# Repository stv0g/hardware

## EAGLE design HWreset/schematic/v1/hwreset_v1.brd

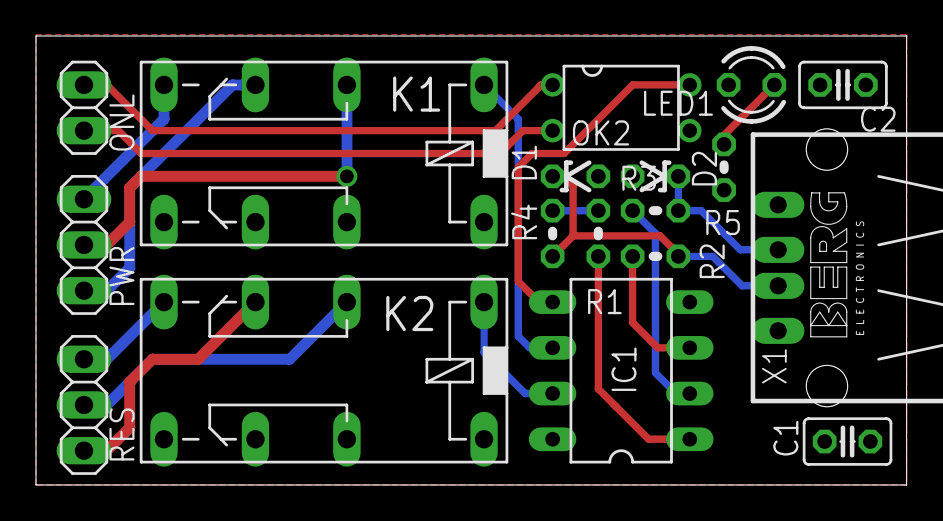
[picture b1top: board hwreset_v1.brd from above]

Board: 2 copper layers, 48.4 x 24.9 mm, 18 parts (0 on the bottom side), 19 nets.

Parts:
C1, C2: 100n; C025-025X050
D1, D2: 3.3; ZDIO-2.5
IC1: TINY22P; DIL08
K1, K2: 351
LED1: LED3MM
OK2: SFH618A-3; DIP4
ONL: 1X02
PWR: 1X03
R1: 5k; 0204V
R2, R3: 68; 0204V
R4: 2k2; 0204V
R5: 200; 0204V
RES: 1X03
X1: PN87520

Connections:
+5V: C1.1, C2.1, IC1.8, R1.1, R4.2, R5.1, X1.1
GND: C1.2, C2.2, D1.A, IC1.4, K1.16, K2.16, LED1.K, OK2.3, X1.4
unnamed: IC1.1, R1.2
unnamed: IC1.6, K1.1
unnamed: K2.P1, RES.2
unnamed: IC1.3, R2.1
unnamed: IC1.2, R3.1
unnamed: K1.P1, PWR.2
unnamed: D1.C, R2.2, R4.1, X1.2
unnamed: D2.C, R3.2, X1.3
unnamed: K1.O1, PWR.1
unnamed: K1.S1, PWR.3
unnamed: K2.O1, RES.1
unnamed: K2.S1, RES.3
unnamed: OK2.1, ONL.2
unnamed: OK2.2, ONL.1
unnamed: IC1.5, OK2.4
unnamed: LED1.A, R5.2
ON: IC1.7, K2.1

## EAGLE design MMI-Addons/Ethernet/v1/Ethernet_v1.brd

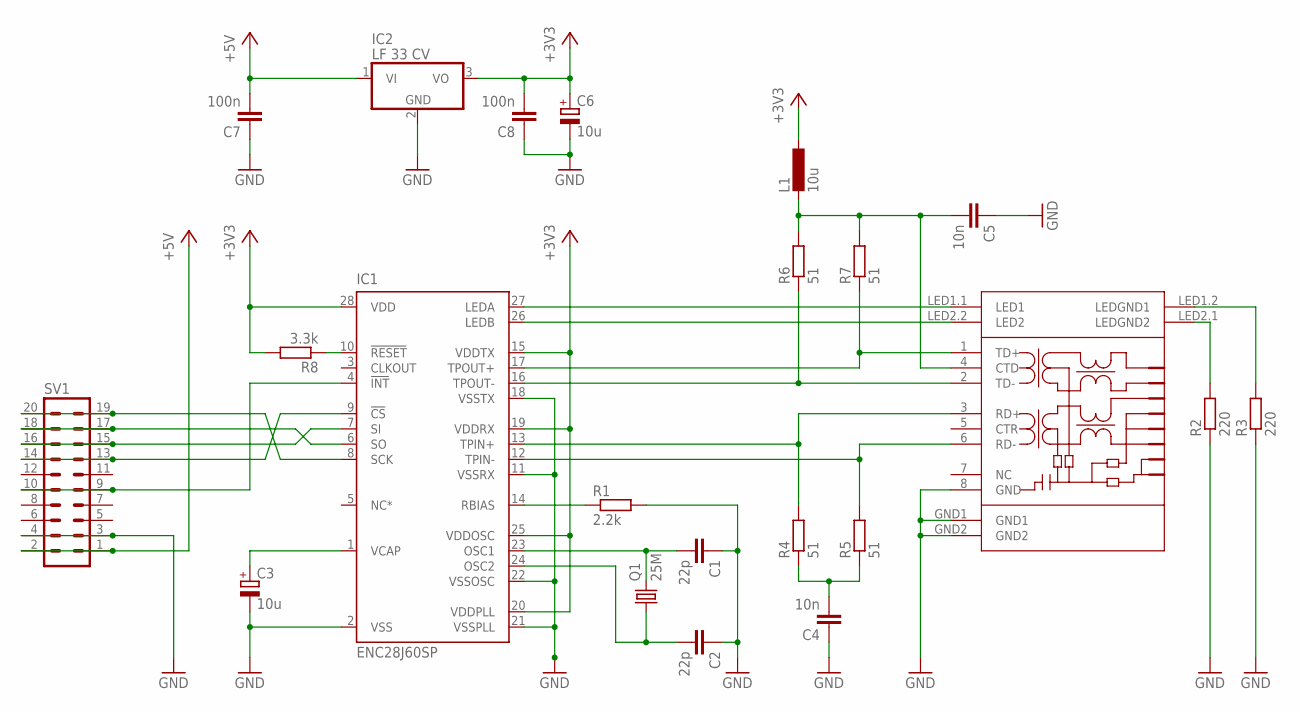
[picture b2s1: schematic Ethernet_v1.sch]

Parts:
C1, C2: 22p; C025-024X044
C3, C6: 10u; E2-5
C4, C5: 10n; C025-025X050
C7, C8: 100n; C025-025X050
IC1: ENC28J60SP; DIL28-3
IC2: LF 33 CV; TO220V
L1: 10u; 0207/10
Q1: 25M; HC49U-V
R1: 2.2k; 0207/2V
R2, R3: 220; 0207/2V
R4, R5, R6, R7: 51; 0207/2V
R8: 3.3k; 0207/2V
SV1: MA10-2W
U$1: TRJ0011

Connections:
+3V3: C6.+, C8.2, IC1.15 (VDDTX), IC1.19 (VDDRX), IC1.20 (VDDPLL), IC1.25 (VDDOSC), IC1.28 (VDD), IC2.3 (VO), L1.1, R8.2
+5V: C7.2, IC2.1 (VI), SV1.1, SV1.2
GND: C1.1, C2.1, C3.-, C4.1, C5.1, C6.-, C7.1, C8.1, IC1.2 (VSS), IC1.11 (VSSRX), IC1.18 (VSSTX), IC1.21 (VSSPLL), IC1.22 (VSSOSC), IC2.2 (GND), R1.2, R2.1, R3.1, SV1.3, SV1.4, U$1.8 (GND), U$1.GND1, U$1.GND2
unnamed: IC1.27 (LEDA), U$1.LED1.1 (LED1)
unnamed: IC1.26 (LEDB), U$1.LED2.2 (LED2)
unnamed: IC1.17 (TPOUT+), R7.1, U$1.1 (TD+)
unnamed: IC1.16 (TPOUT-), R6.1, U$1.2 (TD-)
unnamed: IC1.13 (TPIN+), R4.2, U$1.3 (RD+)
unnamed: IC1.12 (TPIN-), R5.2, U$1.6 (RD-)
unnamed: R2.2, U$1.LED2.1 (LEDGND2)
unnamed: C1.2, IC1.23 (OSC1), Q1.2
unnamed: IC1.14 (RBIAS), R1.1
unnamed: C2.2, IC1.24 (OSC2), Q1.1
unnamed: R3.2, U$1.LED1.2 (LEDGND1)
unnamed: C3.+, IC1.1 (VCAP)
unnamed: C4.2, R4.1, R5.1
unnamed: C5.2, L1.2, R6.2, R7.2, U$1.4 (CTD)
unnamed: IC1.10 (!RESET), R8.1
unnamed: IC1.4 (!INT), SV1.9, SV1.10
unnamed: IC1.8 (SCK), SV1.19, SV1.20
unnamed: IC1.6 (SO), SV1.17, SV1.18
unnamed: IC1.7 (SI), SV1.15, SV1.16
unnamed: IC1.9 (!CS), SV1.13, SV1.14

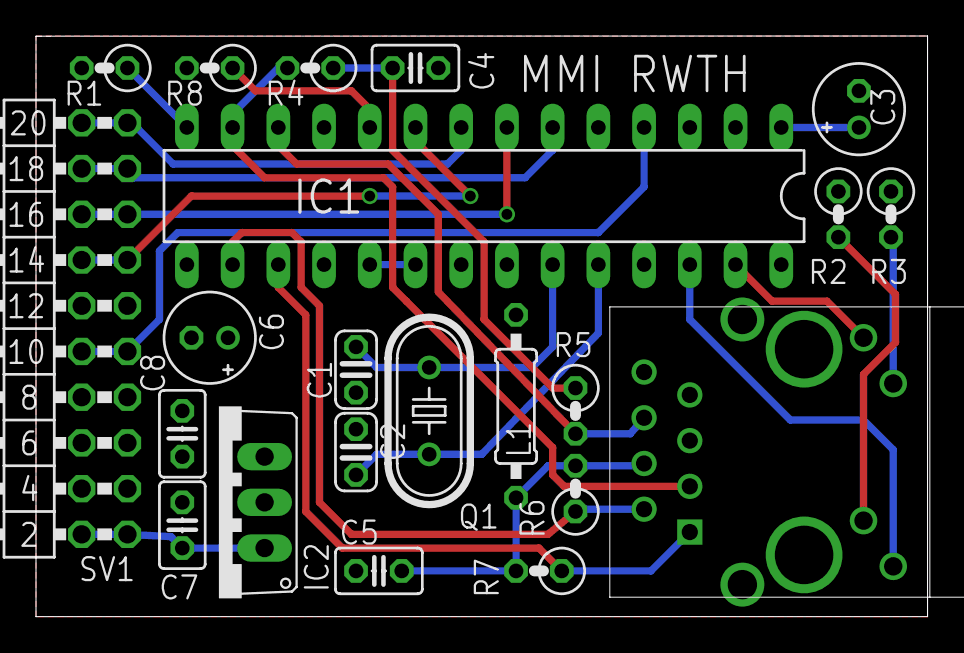
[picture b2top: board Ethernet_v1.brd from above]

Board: 2 copper layers, 49.5 x 32.3 mm, 22 parts (0 on the bottom side), 23 nets.

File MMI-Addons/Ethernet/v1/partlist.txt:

Partlist

Exported from Ethernet_v1.sch at 04.01.14 23:29

EAGLE Version 6.1.0 Copyright (c) 1988-2012 CadSoft

Assembly variant: 

Part     Value          Device          Package      Library   Sheet

C1       22p            C-EU025-024X044 C025-024X044 rcl       1
C2       22p            C-EU025-024X044 C025-024X044 rcl       1
C3       10u            CPOL-EUE2-5     E2-5         rcl       1
C4       10n            C-EU025-025X050 C025-025X050 rcl       1
C5       10n            C-EU025-025X050 C025-025X050 rcl       1
C6       10u            CPOL-EUE2-5     E2-5         rcl       1
C7       100n           C-EU025-025X050 C025-025X050 rcl       1
C8       100n           C-EU025-025X050 C025-025X050 rcl       1
IC1      ENC28J60SP     ENC28J60SP      DIL28-3      microchip 1
IC2      LF 33 CV       788TV           TO220V       linear    1
L1       10u            L-EU0207/10     0207/10      rcl       1
Q1       25M            CRYSTALHC49U-V  HC49U-V      crystal   1
R1       2.2k           R-EU_0207/2V    0207/2V      rcl       1
R2       220            R-EU_0207/2V    0207/2V      rcl       1
R3       220            R-EU_0207/2V    0207/2V      rcl       1
R4       51             R-EU_0207/2V    0207/2V      rcl       1
R5       51             R-EU_0207/2V    0207/2V      rcl       1
R6       51             R-EU_0207/2V    0207/2V      rcl       1
R7       51             R-EU_0207/2V    0207/2V      rcl       1
R8       3.3k           R-EU_0207/2V    0207/2V      rcl       1
SV1                     MA10-2W         MA10-2W      con-lstb  1
U$1      TRJ0011        TRJ0011         TRJ0011      Ethernet2 1

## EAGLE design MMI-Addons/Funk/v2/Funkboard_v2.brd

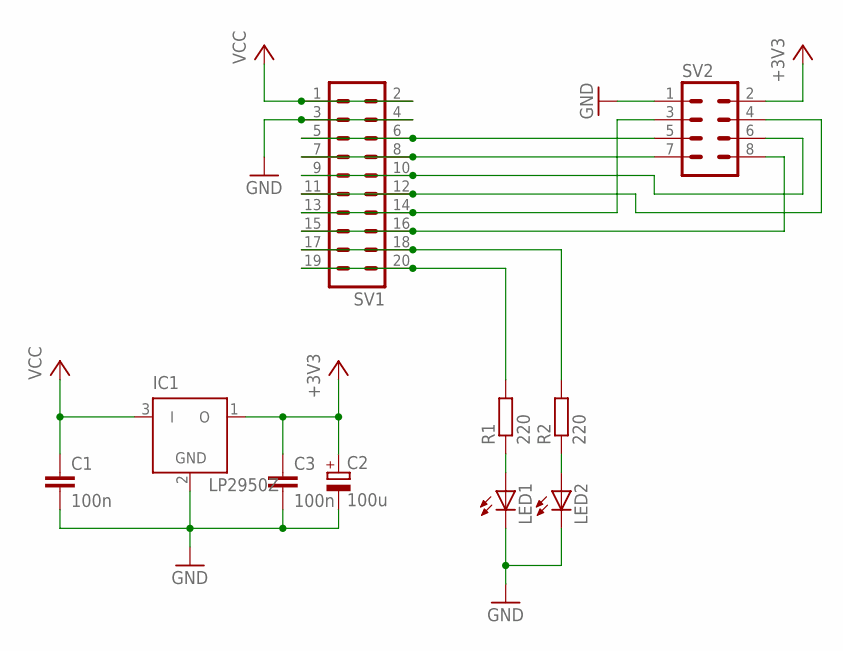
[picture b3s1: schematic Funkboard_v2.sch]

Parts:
C1, C3: 100n; C025-025X050
C2: 100u; E2,5-6
IC1: LP2950Z; TO92
LED1, LED2: LED3MM
R1, R2: 220; 0204V
SV1: MA10-2W
SV2: MA04-2

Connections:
+3V3: C2.+, C3.1, IC1.1 (O), SV2.2
GND: C1.2, C2.-, C3.2, IC1.2 (GND), LED1.K (C), LED2.K (C), SV1.3, SV1.4, SV2.1
unnamed: LED1.A, R1.1
unnamed: LED2.A, R2.1
unnamed: SV1.5, SV1.6, SV2.5
unnamed: SV1.7, SV1.8, SV2.7
unnamed: SV1.9, SV1.10, SV2.6
unnamed: SV1.11, SV1.12, SV2.4
unnamed: SV1.13, SV1.14, SV2.3
unnamed: SV1.15, SV1.16, SV2.8
unnamed: R2.2, SV1.17, SV1.18
unnamed: R1.2, SV1.19, SV1.20
VCC: C1.1, IC1.3 (I), SV1.1, SV1.2

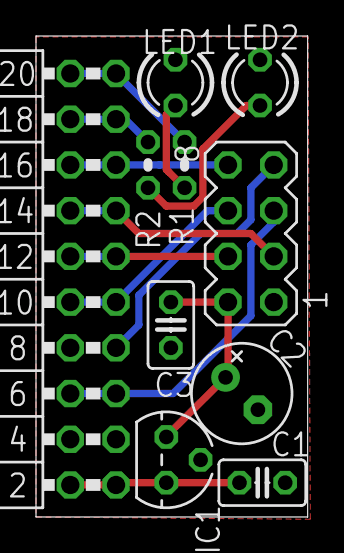
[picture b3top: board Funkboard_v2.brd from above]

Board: 2 copper layers, 15.1 x 26.7 mm, 10 parts (0 on the bottom side), 13 nets.

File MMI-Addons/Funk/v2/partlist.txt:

Partlist

Exported from Funkboard_v2.sch at 04.01.14 20:28

EAGLE Version 6.1.0 Copyright (c) 1988-2012 CadSoft

Assembly variant: 

Part     Value          Device          Package      Library  Sheet

C1       100n           C-EU025-025X050 C025-025X050 rcl      1
C2       100u           CPOL-EUE2.5-6   E2,5-6       rcl      1
C3       100n           C-EU025-025X050 C025-025X050 rcl      1
IC1      LP2950Z        LP2950Z         TO92         linear   1
LED1                    LED3MM          LED3MM       led      1
LED2                    LED3MM          LED3MM       led      1
R1       220            R-EU_0204/2V    0204V        rcl      1
R2       220            R-EU_0204/2V    0204V        rcl      1
SV1                     MA10-2W         MA10-2W      con-lstb 1
SV2                     MA04-2          MA04-2       con-lstb 1

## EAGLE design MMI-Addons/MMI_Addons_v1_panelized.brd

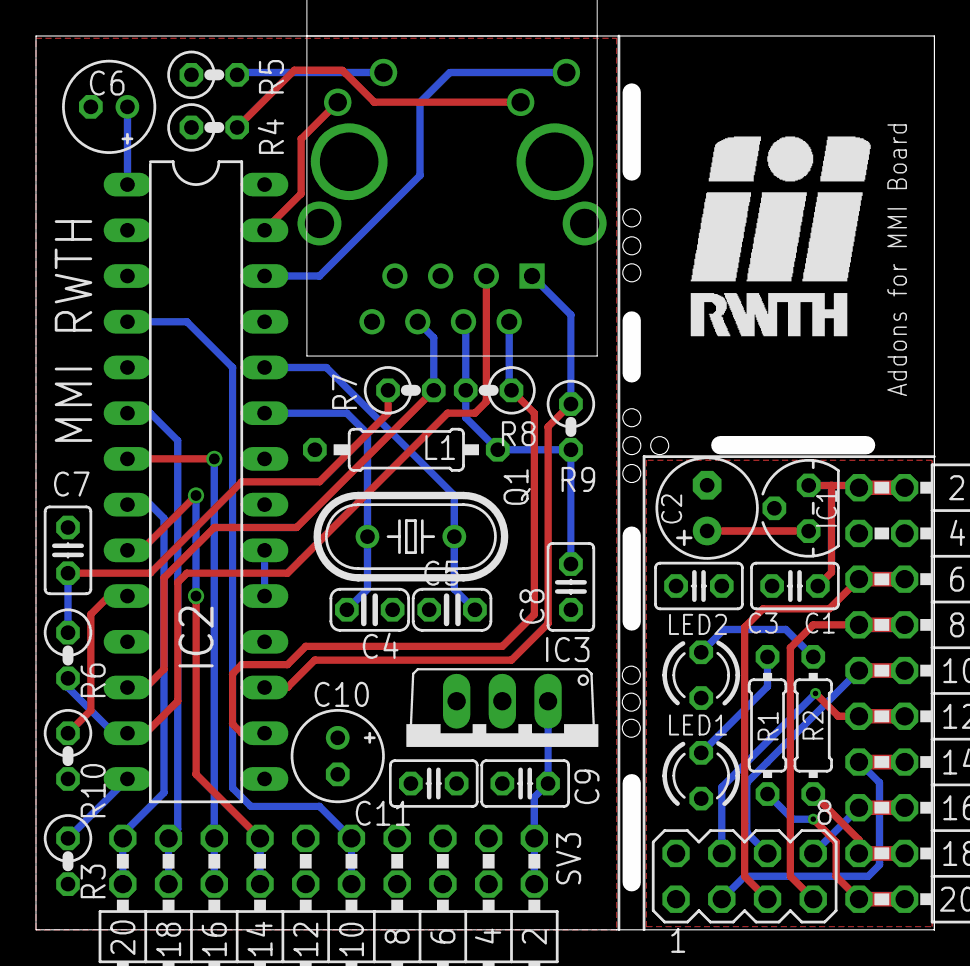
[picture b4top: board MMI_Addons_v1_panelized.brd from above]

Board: 2 copper layers, 49.9 x 49.7 mm, 32 parts (0 on the bottom side), 36 nets.

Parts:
C1, C3, C9, C11: 100n; C025-025X050
C2: 100u; E2,5-6
C4, C5: 22p; C025-024X044
C6, C10: 10u; E2-5
C7, C8: 10n; C025-025X050
IC1: LP2950Z; TO92
IC2: ENC28J60SP; DIL28-3
IC3: LF 33 CV; TO220V
L1: 10u; 0207/10
LED1, LED2: LED3MM
Q1: 25M; HC49U-V
R1, R2: 220; 0204/7
R3: 2.2k; 0207/2V
R4, R5: 220; 0207/2V
R6, R7, R8, R9: 51; 0207/2V
R10: 3.3k; 0207/2V
SV1, SV3: MA10-2W
SV2: MA04-2
U$1: TRJ0011

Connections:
+3V1: C10.+, C11.2, IC2.15, IC2.19, IC2.20, IC2.25, IC2.28, IC3.3, L1.1, R10.2
+3V3: C2.+, C3.1, IC1.1, SV2.2
+5V: C9.2, IC3.1, SV3.1, SV3.2
GND: C1.2, C2.-, C3.2, IC1.2, LED1.K, LED2.K, SV1.3, SV1.4, SV2.1
GND1: C4.1, C5.1, C6.-, C7.1, C8.1, C9.1, C10.-, C11.1, IC2.2, IC2.11, IC2.18, IC2.21, IC2.22, IC3.2, R3.2, R4.1, R5.1, SV3.3, SV3.4, U$1.8, U$1.GND1, U$1.GND2
unnamed: LED1.A, R1.1
unnamed: LED2.A, R2.1
unnamed: SV1.5, SV1.6, SV2.5
unnamed: SV1.7, SV1.8, SV2.7
unnamed: SV1.9, SV1.10, SV2.6
unnamed: SV1.11, SV1.12, SV2.4
unnamed: SV1.13, SV1.14, SV2.3
unnamed: SV1.15, SV1.16, SV2.8
unnamed: R2.2, SV1.17, SV1.18
unnamed: R1.2, SV1.19, SV1.20
unnamed: IC2.27, U$1.LED1.1
unnamed: IC2.26, U$1.LED2.2
unnamed: IC2.17, R9.1, U$1.1
unnamed: IC2.16, R8.1, U$1.2
unnamed: IC2.13, R6.2, U$1.3
unnamed: IC2.12, R7.2, U$1.6
unnamed: IC2.14, R3.1
unnamed: C4.2, IC2.23, Q1.2
unnamed: C5.2, IC2.24, Q1.1
unnamed: R4.2, U$1.LED2.1
unnamed: R5.2, U$1.LED1.2
unnamed: C6.+, IC2.1
unnamed: C7.2, R6.1, R7.1
unnamed: C8.2, L1.2, R8.2, R9.2, U$1.4
unnamed: IC2.10, R10.1
unnamed: IC2.8, SV3.19, SV3.20
unnamed: IC2.6, SV3.17, SV3.18
unnamed: IC2.7, SV3.15, SV3.16
unnamed: IC2.9, SV3.13, SV3.14
unnamed: IC2.4, SV3.9, SV3.10
VCC: C1.1, IC1.3, SV1.1, SV1.2

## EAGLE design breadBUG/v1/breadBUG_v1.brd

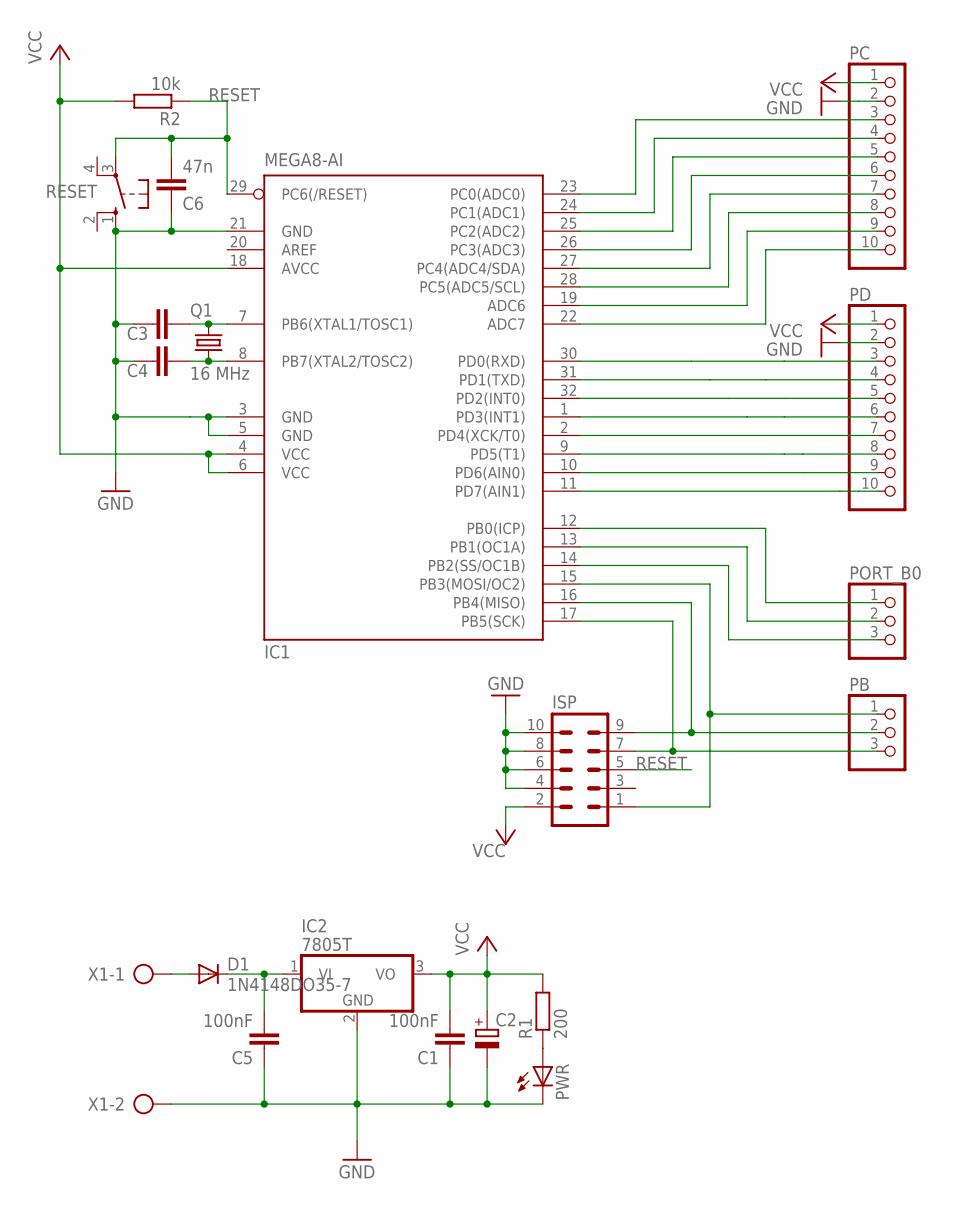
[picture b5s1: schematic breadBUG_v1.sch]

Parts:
C1, C5: 100nF; C2.5-2
C2: CPOL-EUE2.5-6; E2,5-6
C3, C4: C-EU025-025X050; C025-025X050
C6: 47n; C025-025X050
D1: 1N4148DO35-7; DO35-7
IC1: MEGA8-AI; TQFP32-08
IC2: 7805T; TO220H
ISP: MA05-2
PB: PINHD-1X3; 1X03
PC: PINHD-1X10; 1X10
PD: PINHD-1X10; 1X10
PORT_B0: PINHD-1X3; 1X03
PWR: LED3MM
Q1: 16 MHz; HC49U-V
R1: 200; 0204V
R2: 10k; 0204V
RESET: 10-XX; B3F-10XX; MPN B3F-1000
X1: AK500/2

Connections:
GND: C1.1, C2.-, C3.1, C4.1, C5.1, C6.1, IC1.3 (GND), IC1.5 (GND), IC1.21 (GND), IC2.2 (GND), ISP.4, ISP.6, ISP.8, ISP.10, PC.2, PD.2, PWR.K (C), RESET.1 (S), X1.2
unnamed: C3.2, IC1.7 (PB6(XTAL1/TOSC1)), Q1.2
unnamed: C4.2, IC1.8 (PB7(XTAL2/TOSC2)), Q1.1
unnamed: PWR.A, R1.1
unnamed: C5.2, D1.C, IC2.1 (VI)
unnamed: D1.A, X1.1
PB0: IC1.12 (PB0(ICP)), PORT_B0.1
PB1: IC1.13 (PB1(OC1A)), PORT_B0.2
PB2: IC1.14 (PB2(SS/OC1B)), PORT_B0.3
PB3: IC1.15 (PB3(MOSI/OC2)), ISP.1, PB.1
PB4: IC1.16 (PB4(MISO)), ISP.9, PB.2
PB5: IC1.17 (PB5(SCK)), ISP.7, PB.3
PC0: IC1.23 (PC0(ADC0)), PC.3
PC1: IC1.24 (PC1(ADC1)), PC.4
PC2: IC1.25 (PC2(ADC2)), PC.5
PC3: IC1.26 (PC3(ADC3)), PC.6
PC4: IC1.27 (PC4(ADC4/SDA)), PC.7
PC5: IC1.28 (PC5(ADC5/SCL)), PC.8
PC6: IC1.19 (ADC6), PC.9
PC7: IC1.22 (ADC7), PC.10
PD0: IC1.30 (PD0(RXD)), PD.3
PD1: IC1.31 (PD1(TXD)), PD.4
PD2: IC1.32 (PD2(INT0)), PD.5
PD3: IC1.1 (PD3(INT1)), PD.6
PD4: IC1.2 (PD4(XCK/T0)), PD.7
PD5: IC1.9 (PD5(T1)), PD.8
PD6: IC1.10 (PD6(AIN0)), PD.9
PD7: IC1.11 (PD7(AIN1)), PD.10
RESET: C6.2, IC1.29 (PC6(/RESET)), ISP.5, R2.1, RESET.3
VCC: C1.2, C2.+, IC1.4 (VCC), IC1.6 (VCC), IC1.18 (AVCC), IC2.3 (VO), ISP.2, PC.1, PD.1, R1.2, R2.2

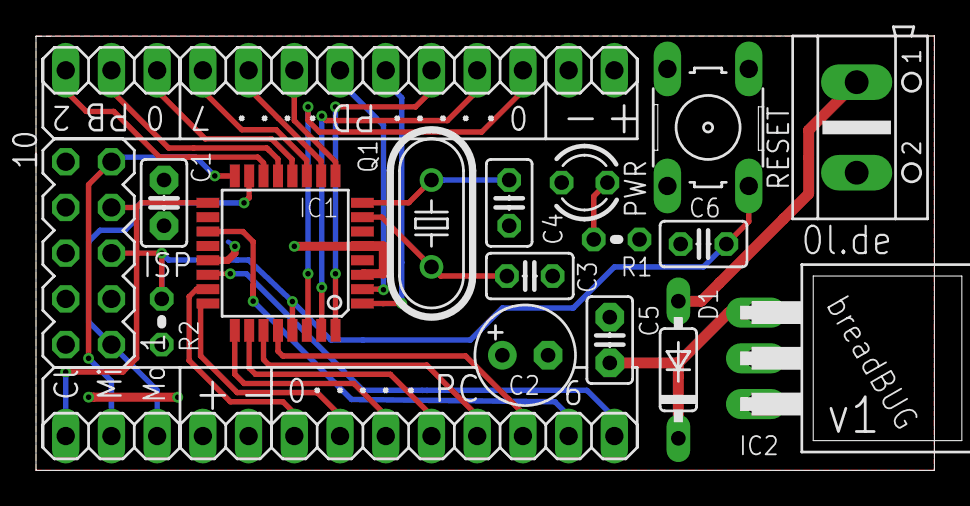
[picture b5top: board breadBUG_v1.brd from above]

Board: 2 copper layers, 49.9 x 24.1 mm, 20 parts (0 on the bottom side), 30 nets.

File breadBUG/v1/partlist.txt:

Partlist

Exported from breadBUG_v1.sch at 04.01.14 20:19

EAGLE Version 6.1.0 Copyright (c) 1988-2012 CadSoft

Assembly variant: 

Part     Value          Device          Package      Library        Sheet

C1       100nF          C2.5/2          C2.5-2       capacitor-wima 1
C2                      CPOL-EUE2.5-6   E2,5-6       rcl            1
C3                      C-EU025-025X050 C025-025X050 rcl            1
C4                      C-EU025-025X050 C025-025X050 rcl            1
C5       100nF          C2.5/2          C2.5-2       capacitor-wima 1
C6       47n            C-EU025-025X050 C025-025X050 rcl            1
D1       1N4148DO35-7   1N4148DO35-7    DO35-7       diode          1
IC1      MEGA8-AI       MEGA8-AI        TQFP32-08    atmel          1
IC2      7805T          7805T           TO220H       linear         1
ISP                     MA05-2          MA05-2       con-lstb       1
PB                      PINHD-1X3       1X03         pinhead        1
PC                      PINHD-1X10      1X10         pinhead        1
PD                      PINHD-1X10      1X10         pinhead        1
PORT_B0                 PINHD-1X3       1X03         pinhead        1
PWR                     LED3MM          LED3MM       led            1
Q1       16 MHz         CRYSTALHC49U-V  HC49U-V      crystal        1
R1       200            R-EU_0204/2V    0204V        rcl            1
R2       10k            R-EU_0204/2V    0204V        rcl            1
RESET                   10-XX           B3F-10XX     switch-omron   1
X1                      AK500/2         AK500/2      con-ptr500     1

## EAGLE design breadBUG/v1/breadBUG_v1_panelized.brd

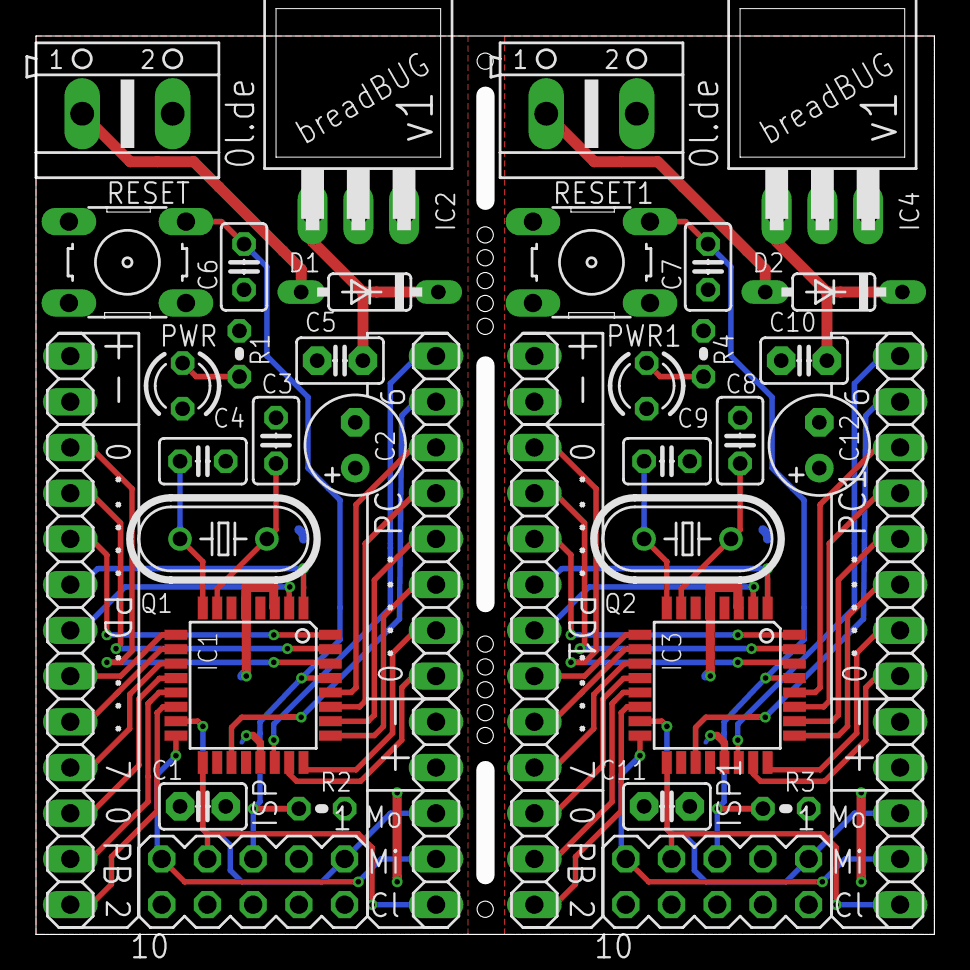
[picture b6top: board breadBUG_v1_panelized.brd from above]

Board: 2 copper layers, 49.9 x 49.9 mm, 40 parts (0 on the bottom side), 60 nets.

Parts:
C1, C5, C10, C11: 100nF; C2.5-2
C2, C12: E2,5-6
C3, C4, C8, C9: C025-025X050
C6, C7: 47n; C025-025X050
D1, D2: 1N4148DO35-7; DO35-7
IC1, IC3: MEGA8-AI; TQFP32-08
IC2, IC4: 7805T; TO220H
ISP, ISP1: MA05-2
PB, PB1: 1X03
PC, PC1: 1X10
PD, PD1: 1X10
PORT_B0, PORT_B1: 1X03
PWR, PWR1: LED3MM
Q1, Q2: 16 MHz; HC49U-V
R1, R4: 200; 0204V
R2, R3: 10k; 0204V
RESET, RESET1: B3F-10XX
X1, X2: AK500/2

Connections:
GND: C1.1, C2.-, C3.1, C4.1, C5.1, C6.1, IC1.3, IC1.5, IC1.21, IC2.2, ISP.4, ISP.6, ISP.8, ISP.10, PC.2, PD.2, PWR.K, RESET.1, X1.2
GND1: C7.1, C8.1, C9.1, C10.1, C11.1, C12.-, IC3.3, IC3.5, IC3.21, IC4.2, ISP1.4, ISP1.6, ISP1.8, ISP1.10, PC1.2, PD1.2, PWR1.K, RESET1.1, X2.2
unnamed: PWR1.A, R4.1
unnamed: C3.2, IC1.7, Q1.2
unnamed: C4.2, IC1.8, Q1.1
unnamed: PWR.A, R1.1
unnamed: C10.2, D2.C, IC4.1
unnamed: D2.A, X2.1
unnamed: C5.2, D1.C, IC2.1
unnamed: D1.A, X1.1
unnamed: C9.2, IC3.8, Q2.1
unnamed: C8.2, IC3.7, Q2.2
PB0: IC1.12, PORT_B0.1
PB1: IC1.13, PORT_B0.2
PB2: IC1.14, PORT_B0.3
PB3: IC1.15, ISP.1, PB.1
PB4: IC1.16, ISP.9, PB.2
PB5: IC1.17, ISP.7, PB.3
PB6: IC3.16, ISP1.9, PB1.2
PB7: IC3.17, ISP1.7, PB1.3
PB8: IC3.12, PORT_B1.1
PB9: IC3.13, PORT_B1.2
PB10: IC3.14, PORT_B1.3
PB11: IC3.15, ISP1.1, PB1.1
PC0: IC1.23, PC.3
PC1: IC1.24, PC.4
PC2: IC1.25, PC.5
PC3: IC1.26, PC.6
PC4: IC1.27, PC.7
PC5: IC1.28, PC.8
PC6: IC1.19, PC.9
PC7: IC1.22, PC.10
PC8: IC3.23, PC1.3
PC9: IC3.24, PC1.4
PC10: IC3.25, PC1.5
PC11: IC3.26, PC1.6
PC12: IC3.27, PC1.7
PC13: IC3.28, PC1.8
PC14: IC3.19, PC1.9
PC15: IC3.22, PC1.10
PD0: IC1.30, PD.3
PD1: IC1.31, PD.4
PD2: IC1.32, PD.5
PD3: IC1.1, PD.6
PD4: IC1.2, PD.7
PD5: IC1.9, PD.8
PD6: IC1.10, PD.9
PD7: IC1.11, PD.10
PD8: IC3.11, PD1.10
PD9: IC3.10, PD1.9
PD10: IC3.9, PD1.8
PD11: IC3.2, PD1.7
PD12: IC3.1, PD1.6
PD13: IC3.32, PD1.5
PD14: IC3.31, PD1.4
PD15: IC3.30, PD1.3
RESET: C6.2, IC1.29, ISP.5, R2.1, RESET.3
RESET1: C7.2, IC3.29, ISP1.5, R3.1, RESET1.3
VCC: C1.2, C2.+, IC1.4, IC1.6, IC1.18, IC2.3, ISP.2, PC.1, PD.1, R1.2, R2.2
VCC1: C11.2, C12.+, IC3.4, IC3.6, IC3.18, IC4.3, ISP1.2, PC1.1, PD1.1, R3.2, R4.2
